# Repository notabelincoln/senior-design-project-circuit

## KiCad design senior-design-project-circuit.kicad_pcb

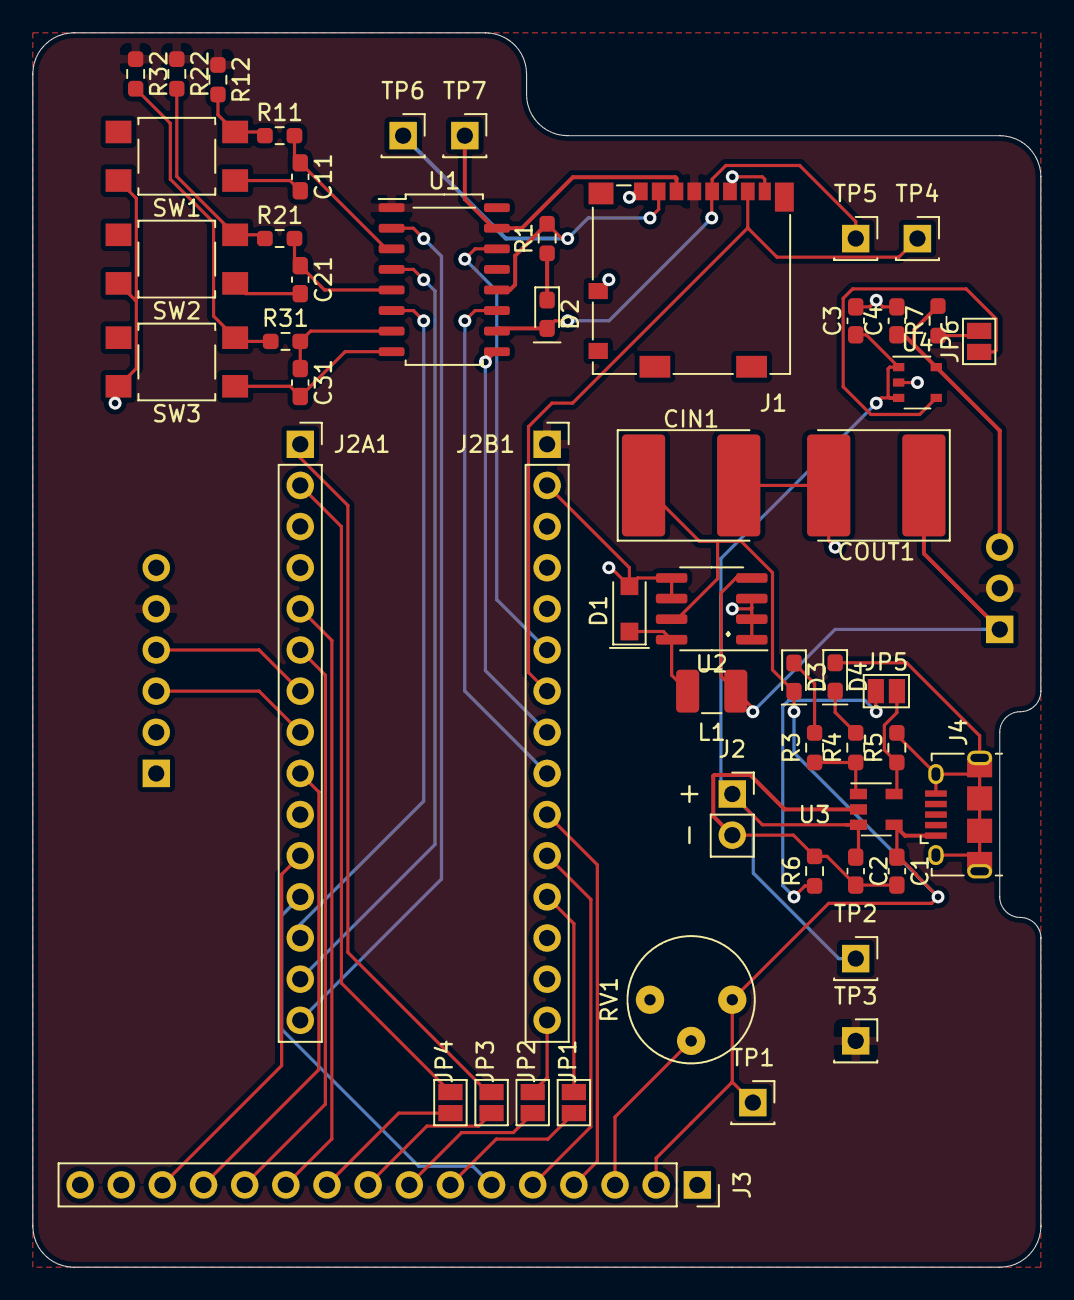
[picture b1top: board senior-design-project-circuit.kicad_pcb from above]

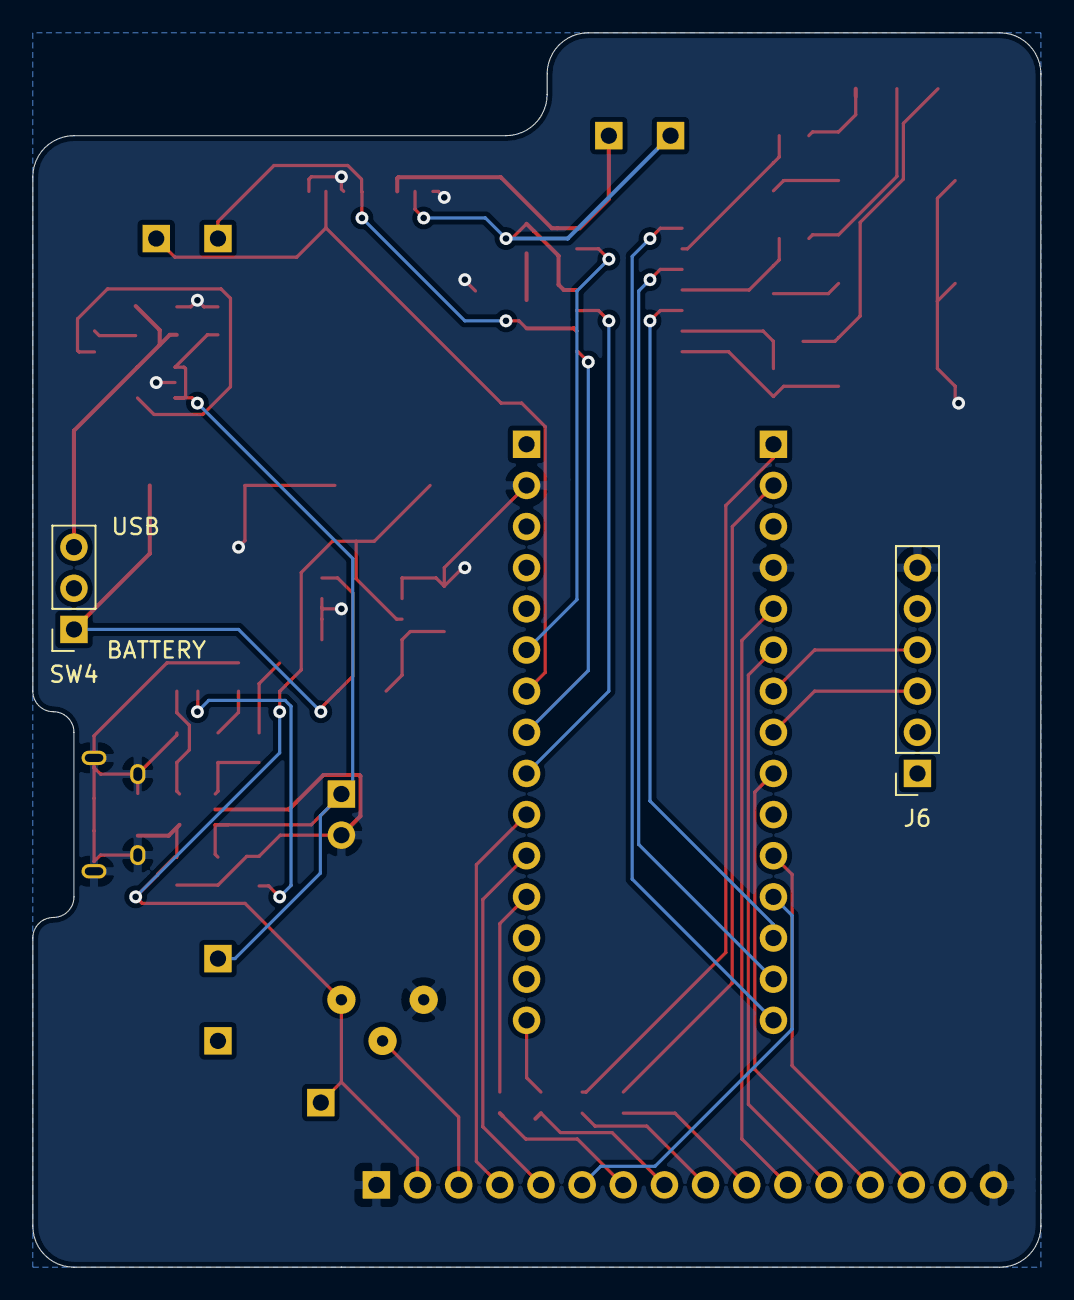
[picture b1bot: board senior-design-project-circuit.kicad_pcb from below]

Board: 2 copper layers, 62.2 x 76.2 mm, 55 parts (2 on the bottom side), 48 nets.

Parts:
C1, C2: 10p; C_0603_1608Metric_Pad1.08x0.95mm_HandSolder
C3, C4: 1u; C_0603_1608Metric_Pad1.08x0.95mm_HandSolder
C11, C21, C31: 100nF; C_0603_1608Metric_Pad1.08x0.95mm_HandSolder
CIN1: 120uF; CP_EIA-7260-38_AVX-R_Pad2.68x6.30mm_HandSolder
COUT1: 33uF; CP_EIA-7260-15_AVX-R_Pad2.68x6.30mm_HandSolder
D1: SM5817PL; D_SOD-123F
D2: LED3; LED_0603_1608Metric_Pad1.05x0.95mm_HandSolder
D3: LED1; LED_0603_1608Metric_Pad1.05x0.95mm_HandSolder
D4: LED2; LED_0603_1608Metric_Pad1.05x0.95mm_HandSolder
J1: Micro_SD_Card; microSD_HC_Molex_104031-0811
J2: Conn_01x02_Female; PinSocket_1x02_P2.54mm_Vertical
J2A1, J2B1: Conn_01x15_Female; PinSocket_1x15_P2.54mm_Vertical
J3: Conn_01x16_Male; PinSocket_1x16_P2.54mm_Vertical
J4: USB_B_Micro; USB_Micro-B_Amphenol_10118194_Horizontal
J6: Conn_01x06_Female; PinSocket_1x06_P2.54mm_Vertical
JP1, JP2, JP3, JP4, JP5, JP6: SolderJumper_2_Open; SolderJumper-2_P1.3mm_Open_Pad1.0x1.5mm
L1: 27uH; L_1210_3225Metric_Pad1.42x2.65mm_HandSolder
R1: 1k; R_0603_1608Metric_Pad0.98x0.95mm_HandSolder
R3, R4: 470; R_0603_1608Metric_Pad0.98x0.95mm_HandSolder
R5, R7: 10k; R_0603_1608Metric_Pad0.98x0.95mm_HandSolder
R6: 2.5k; R_0603_1608Metric_Pad0.98x0.95mm_HandSolder
R11, R21, R31: 47k; R_0603_1608Metric_Pad0.98x0.95mm_HandSolder
R12, R22, R32: 20k; R_0603_1608Metric_Pad0.98x0.95mm_HandSolder
RV1: R_POT_US; Potentiometer_Bourns_3339P_Vertical_HandSoldering
SW1, SW2, SW3: SW_Push; SW_SPST_TL3305A
SW4: SW_SPDT_MSM; PinSocket_1x03_P2.54mm_Vertical
TP1, TP2, TP3, TP4, TP5, TP6, TP7: TestPoint; PinSocket_1x01_P2.54mm_Vertical
U1: 4050; SOIC-16_4.55x10.3mm_P1.27mm
U2: LM2594M-3.3; SOIC-8_3.9x4.9mm_P1.27mm
U3: MCP73831-2-OT; SOT-23-5
U4: NCP164ASN330T1G; TSOP-5_1.65x3.05mm_P0.95mm

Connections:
+3V3: C2.1, COUT1.1, J1.4 (VDD), J2B1.1, J6.5, L1.2, R12.1, R22.1, R32.1, SW4.2, TP3.1, U1.1 (VCC), U2.4 (FB), U3.3 (VBAT)
+5V: C1.1, CIN1.1, D3.2 (A), J3.2, J4.1 (VBUS), RV1.1, TP1.1, U2.7 (VIN), U3.4 (VDD)
/+3V7: C3.1, J2.1, TP2.1, U4.1, U4.3
/GPIO_EXTI4: J2A1.15, U1.2
/GPIO_EXTI5: J2A1.14, U1.4
/GPIO_EXTI11: J2A1.13, U1.6
/I2C1_SCL: J2A1.8, J6.3
/I2C1_SDA: J2A1.7, J6.4
/LCD_DB0: J2B1.12, JP1.1 (A)
/LCD_DB1: J2B1.15, JP2.1 (A)
/LCD_DB2: J2A1.1, JP3.1 (A)
/LCD_DB3: J2A1.2, JP4.1 (A)
/LCD_DB4: J2A1.5, J3.11
/LCD_DB5: J2A1.6, J3.12
/LCD_DB6: J2A1.9, J3.13
/LCD_DB7: J2A1.11, J3.14
/LCD_EN: J2A1.12, J3.6
/LCD_RS: J2B1.10, J3.4
/LCD_RW: J2B1.11, J3.5
/SPI1_MISO: J1.7 (DAT0), J2B1.7, TP4.1
/SPI1_MOSI: J2B1.6, U1.14
/SPI1_NSS: J2B1.9, U1.11
/SPI1_SCK: J2B1.8, U1.9
GNDREF: C1.2, C2.2, C3.2, C4.2, C11.2, C21.2, C31.2, CIN1.2, COUT1.2, D1.2 (A), D4.1 (K), J1.1 (DAT2), J1.6 (VSS), J1.8 (DAT1), J1.9 (SHIELD), J2.2, J2A1.4, J2B1.2, J3.1, J3.16, J4.5 (GND), J4.6 (Shield), J6.6, R5.2, R6.2, RV1.3, SW1.1, SW2.1, SW3.1, U1.8 (VSS), U2.1 (NC), U2.2 (NC), U2.3 (NC), U2.5 (~ON/OFF), U2.6 (GND), U3.2 (VSS), U4.2
unnamed: C4.1, R7.2, SW4.3, U4.5
unnamed: C11.1, R11.2, U1.3
unnamed: C21.1, R21.2, U1.5
unnamed: C31.1, R31.2, U1.7
unnamed: D1.1 (K), L1.1, U2.8 (OUT)
unnamed: D2.1 (K), R1.1
unnamed: D2.2 (A), J1.5 (CLK), TP5.1, U1.10
unnamed: D3.1 (K), R3.2
unnamed: D4.2 (A), R4.2
unnamed: J1.2 (DAT3/CD), R1.2, TP6.1, U1.12
unnamed: J1.3 (CMD), TP7.1, U1.15
unnamed: J3.3, RV1.2
unnamed: J3.7, JP1.2 (B)
unnamed: J3.8, JP2.2 (B)
unnamed: J3.9, JP3.2 (B)
unnamed: J3.10, JP4.2 (B)
unnamed: JP5.1 (A), R6.1
unnamed: JP5.2 (B), R5.1, U3.5 (PROG)
unnamed: JP6.1, U4.4
unnamed: JP6.2, R7.1
unnamed: R3.1, R4.1, U3.1 (STAT)
unnamed: R11.1, R12.2, SW1.2
unnamed: R21.1, R22.2, SW2.2
unnamed: R31.1, R32.2, SW3.2

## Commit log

2022-03-24 Added files for circuit design
2022-03-25 Added labels to schematic pin headers
